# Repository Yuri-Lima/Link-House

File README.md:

<!-- Headings --> <!-- Strong --> <!-- Italics --> <!-- Blockquote --> <!-- Links --> <!-- UL --> <!-- OL --> <!-- Images --> <!-- Code Blocks --> <!-- Tables --> 
<!-- Task Lists -->

> # Homefi AX

### The project started in 2014. This project had the intention to created access for home automation to find an of family income population.
The Homefi module was created to be easily installed by users with low knowledge in home electronics. The unique skills  required the user wasi the connection of wires for the system to be installed. The Homefi project was cancelled around at 2016 after the launch of the Chinese module called Sonoff. This module basically does the same service as Homefi AX. **Web site:** [sonoff](https://sonoff.tech/) 

> ### Hardware

1. ESP8266 2.4Ghz board from espressif;
1. Solid States Relays;
1. 100 16v SMD Capacitors;
1. Hi-Link Imput 240Vac to 5Vdc/3w as Power Suply;
1. BC 846 Transistor;</li>
1. DHT11 as Temperature Sensor;
1. Varistor and Inductor as protection of the circuit;
1. General conectors.

> ### Software

1. Eagle to PCB;
1. Arduino IDE;
1. [Onlinegerberviewer](https://onlinegerberviewer.azurewebsites.net/)

> ### Software Main Language Used
* The Arduino IDE supports the languages C and C++ using special rules of code structuring. 
  The Arduino IDE supplies a software library from the Wiring project, which provides many common input and output procedures

> ### Protoypes Images

> ### Contact

> **Atention** If you go email me, please put as subject the name of the project, in this case: **(Homefi AX) Requests**

|  Name |  Email | Mobile  |
|-------|--------|---------|
|  Yuri Lima | y.m.lima19@gmail.com  | +353 83 419.1605  |

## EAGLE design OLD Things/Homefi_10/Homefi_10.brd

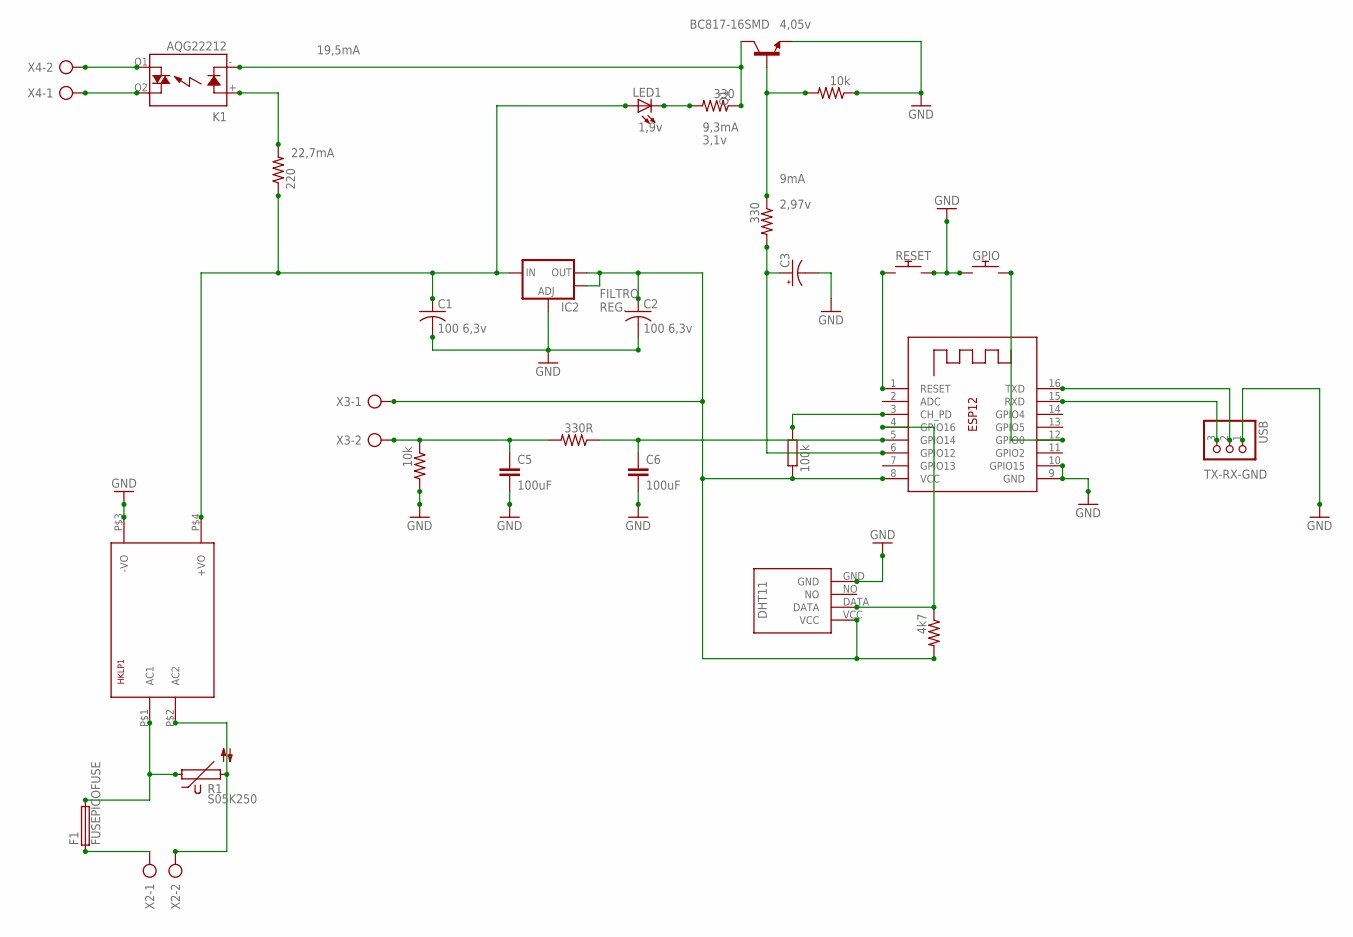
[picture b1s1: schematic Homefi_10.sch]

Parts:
1, 2: 10k; M0805
3: 100k; M0805
4: 330R; M0805
5, 7: 330; M0805
6: 220; M0805
8: 4k7; M0805
C1, C2: 100 6,3v; C0805
C3: CPOL-US153CLV-0605; 153CLV-0605
C5, C6: 100uF; C0805
F1: FUSEPICOFUSE; PICOFUSE
GPIO: GPIO; TACT_PANA-EVQ
HKLP1: HKLPM01
IC2: V_REG_LM1117SOT223; SOT223
K1: AQG22212; AQG
LED1: LEDCHIPLED_0805; CHIPLED_0805
Q1: BC817-16SMD; SOT23-BEC
R1: S05K250
RESET: RESET; TACT_PANA-EVQ
U$1: DHT11-PION.
USB: PINHD-1X3; 1X03
X2, X3, X4: AK500/2
X5: ESP-12

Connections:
2N3904: 5.1, K1.- (K), Q1.C
5V: 6.1, C1.1, HKLP1.P$4 (+VO), IC2.3 (IN), LED1.A
GND: 1.1, 2.2, C1.2, C2.2, C3.-, C5.2, C6.2, GPIO.P$1, HKLP1.P$3 (-VO), IC2.1 (ADJ), Q1.E, RESET.P$2, U$1.GND, USB.1, X5.9 (GND), X5.10 (GPIO15)
unnamed: K1.O1 (DS2), X4.2
unnamed: 3.1, 8.2, C2.1, IC2.2 (OUT), IC2.4 (OUT), U$1.VCC, X3.1, X5.8 (VCC)
unnamed: 5.2, LED1.C
unnamed: K1.O2 (DS1), X4.1
unnamed: 6.2, K1.+ (A)
unnamed: USB.3, X5.15 (RXD)
unnamed: RESET.P$1, X5.1 (RESET)
unnamed: F1.1, X2.1
unnamed: 1.2, 7.1, Q1.B
unnamed: F1.2, HKLP1.P$1 (AC1), R1.1
unnamed: 4.1, C6.1, X5.5 (GPIO14)
unnamed: 2.1, 4.2, C5.1, X3.2
unnamed: 3.2, X5.3 (CH_PD)
unnamed: 7.2, C3.+, X5.6 (GPIO12)
unnamed: HKLP1.P$2 (AC2), R1.2, X2.2
unnamed: 8.1, U$1.DATA, X5.4 (GPIO16)
unnamed: GPIO.P$2, X5.12 (GPIO0)
unnamed: USB.2, X5.16 (TXD)

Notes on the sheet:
FILTRO REG.
TX-RX-GND
9mA
1,9v
9,3mA
22,7mA
19,5mA
2,97v
3,1v
4,05v

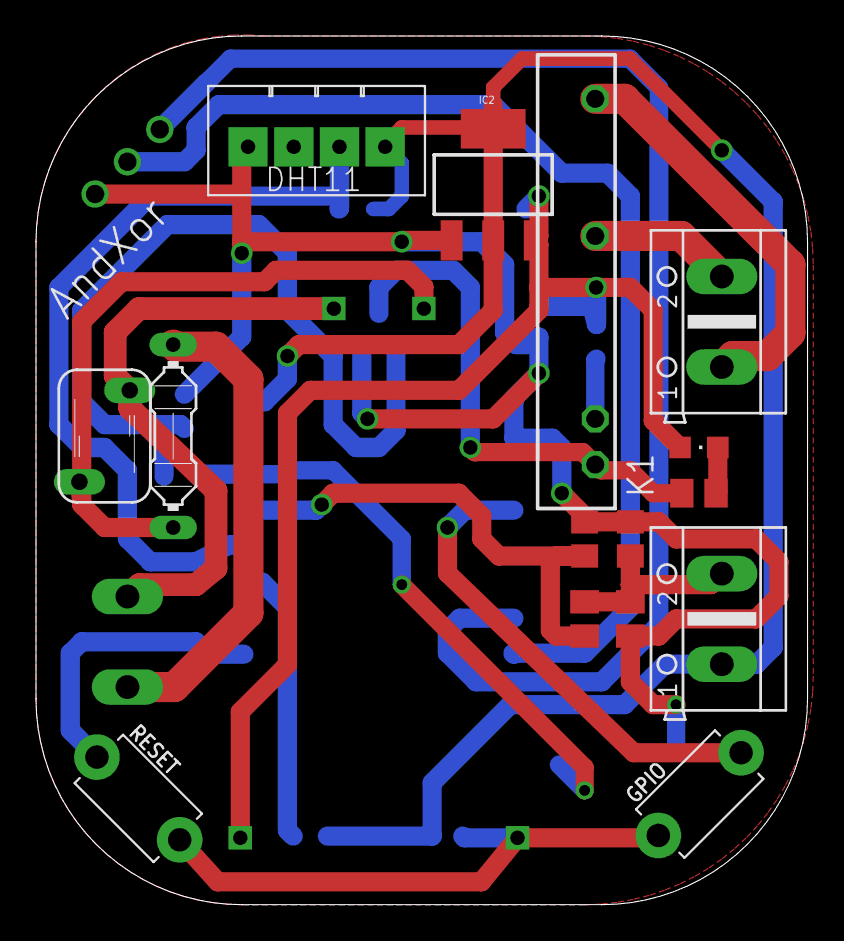
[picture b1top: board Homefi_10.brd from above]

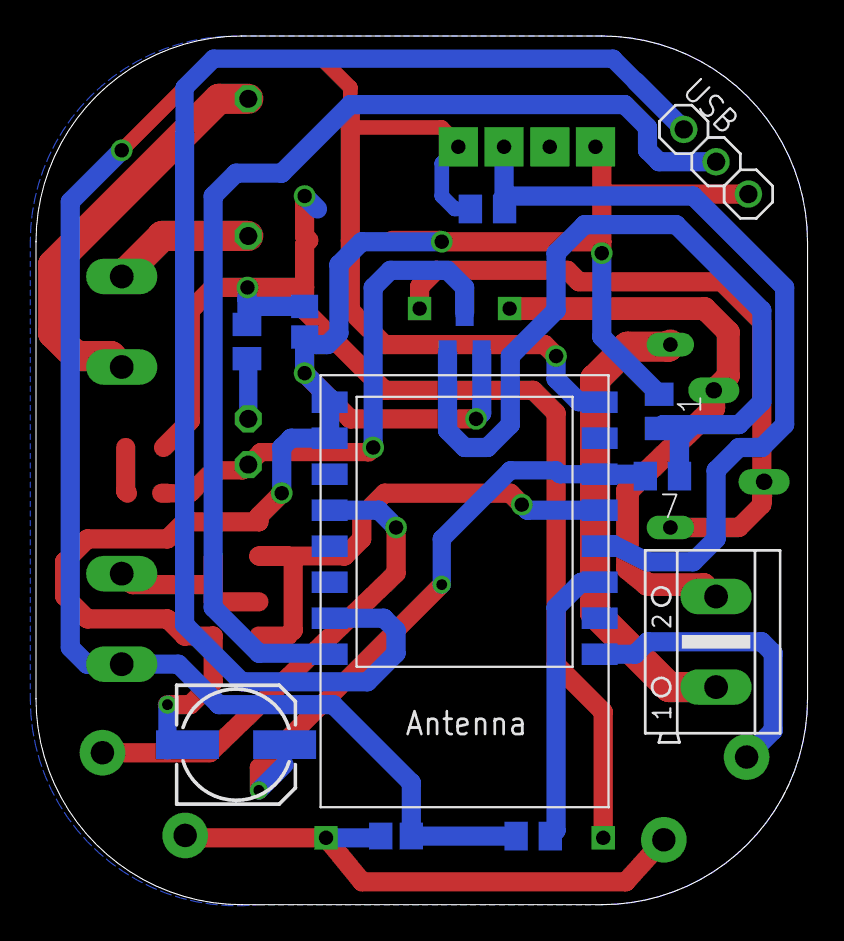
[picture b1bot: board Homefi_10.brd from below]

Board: 2 copper layers, 42.9 x 48.3 mm, 28 parts (12 on the bottom side), 21 nets.

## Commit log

2014-11-26 :lollipop: Added .gitattributes & .gitignore files
2014-11-26 Project Link House
    Residence Automation
2014-11-26 Add more Var of Sensor
2014-11-28 Alterações no HTML Parte 1
2014-11-29 Alterações insignificaticas
2014-11-29 Retirada da EEPROM e testes.
2014-11-29 Simple Timer
    Projeto em produção
2014-11-29 Simple Timer.
2014-11-29 RFID alterações
2014-12-03 Pequenas atualizações
2014-12-04 Testando
2014-12-04 Adicionei a parte de RFid que tinha feito e exclui o .txt de teste
2014-12-04 Atualizações
2014-12-05 Atualizações 2
2014-12-09 Identação
2014-12-13 Atialização
2014-12-15 Atualização RFid ponteiros
2014-12-15 Correções
2014-12-15 Organizando
2014-12-18 Atualização
2014-12-20 Modificações
2014-12-20 Atuallizações recentes!!
2014-12-20 Projeto de Automação Residencial
    Estamos evoluindo no projeto RF_id_Link_House_8 usando o modulo ID12. Já foi criado várias funcionalidades como criação de arquivo em SD_CARD, cadastro de tags no SD, excluir arquivo do SD, desabilit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
2014-12-20 Nova atualização
2014-12-20 Nova atualização 2
2014-12-21 aasdasd
2014-12-21 projeto linkhouse add
2014-12-23 readicionei a pasta de rfid
2014-12-23 Refatorei o código e adicionei a pripriedade da não permissão de cadastro duplicado
2014-12-31 Refatorado! Inclusao de cadastro do nome de Usuarios com a Data
2015-01-02 Refatoração
2015-01-06 refatorado
2015-02-06 Refatorado2
2015-04-08 MP3 Lily PAD
2015-04-12 Refatorado!
2015-10-29 Modificação no Repositorio
2015-10-29 Modificação texto Cod.
2020-07-03 Images
    Few images from the project Homefi AX
2020-07-03 Update README.md
    Include images
2020-07-03 Update README.md
    Created with MarkDown
2020-07-03 Add files via upload
    Test with DataBase

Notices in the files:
parts and their libraries:
SparkFun-PowerIC: Licensing: Creative Commons ShareAlike 4.0 International - https://creativecommons.org/licenses/by-sa/4.0
